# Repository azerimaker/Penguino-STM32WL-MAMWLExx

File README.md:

# Penguino-STM32WL-MAMWLExx
This repo contains all the necessary design and fabrication files for the [Move Solution's MAMWLExx](https://www.hackster.io/move-solutions/design-a-lora-communication-board-based-on-mamwlexx-cbf25c) based Penguino STM32WL breakout board.

MAMWLExx is a very tiny low power radio module, which can be easily integrated into any PCB to enable it for wireless communication. It measures only 15x16mm and features 52 pins out of which 38 are multi-purpose GPIOs.

### Specs (SoC): 
- [STM32WLE5JC](https://www.st.com/en/microcontrollers-microprocessors/stm32wle5jc.html) Wireless SoC
- ARM Cortex M4 ultra-low-power MCU
- Integrated SX1262 RF transciever
- Frequency range: 150 MHz to 960 MHz.
- Modulation: LoRa®, (G)FSK, (G)MSK and BPSK
- Transmitter power: programmable up to +22 dBm 

### Specs ([MAMWLExx module](](https://www.hackster.io/move-solutions/mamwlexx-9f79eb))): 

Board requirements:
- 4 layers, 1.6mm thickness
- 6mil trace/clearance
- 0.3mm drill

### Contact:
If you have any question or comments about the board please feel free to open an issue discussion or drop me a message at [@azerimaker](https://twitter.com/azerimaker). For any specific questions about the module please get in touch with [ Ferdinando Frediani ](https://www.linkedin.com/in/ferdinando-frediani-982807ab/) of Move Solutions, the creators of this awesome module. 

### License:
- Hardware license: CERN-OHL-S v2
- Software license: under MIT unless otherise indicated 
- Documentation license:  CC BY-SA 4.0 International.

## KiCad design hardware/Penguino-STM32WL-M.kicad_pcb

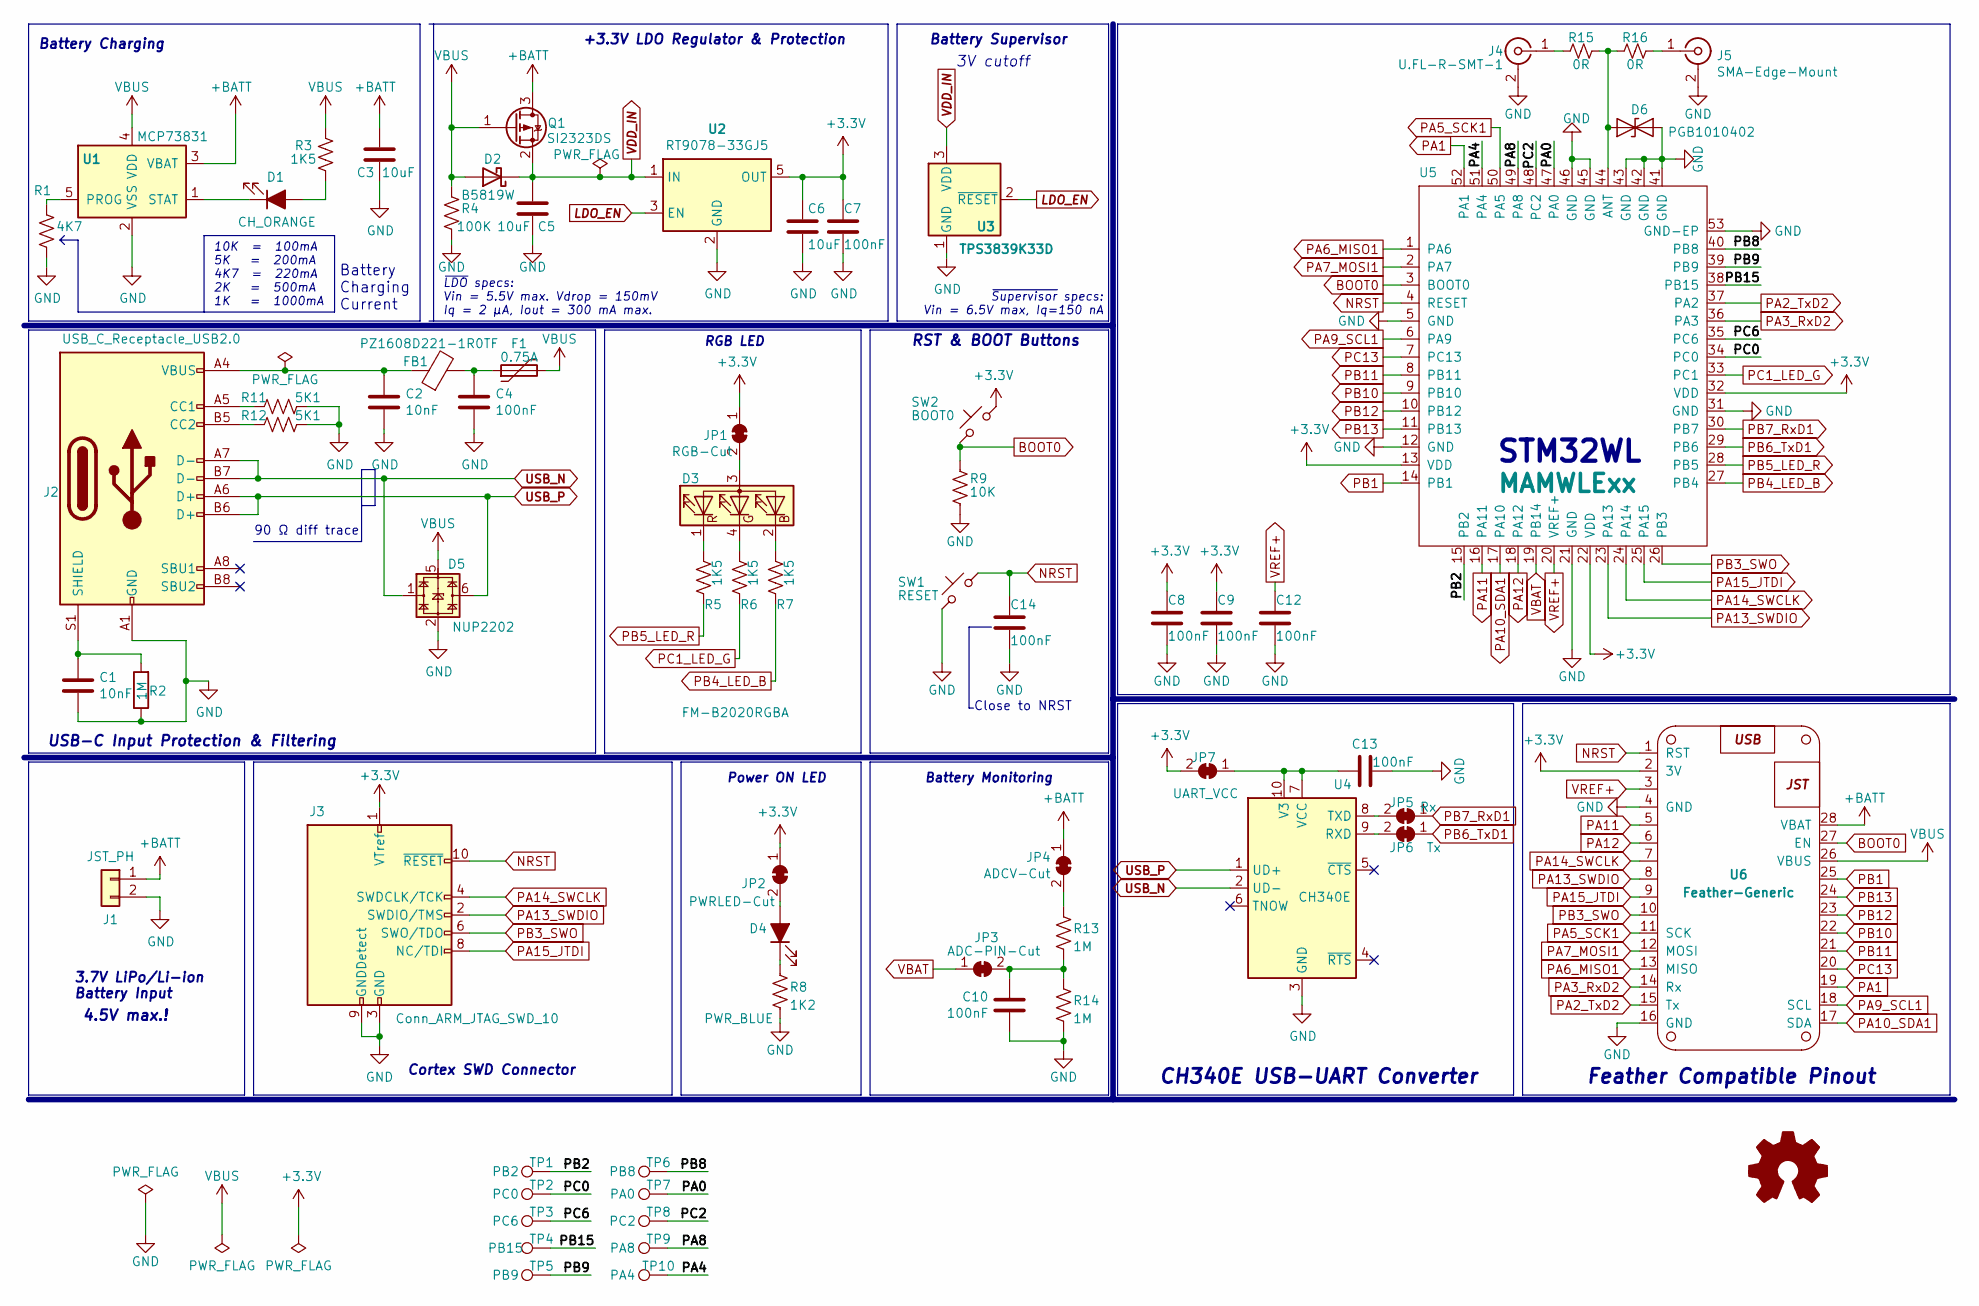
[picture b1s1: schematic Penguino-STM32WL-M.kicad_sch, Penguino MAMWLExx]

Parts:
C1, C2: 10nF; C_0402_1005Metric; MPN CC0402KRX7R9BB103; LCSC_Part# C57112
C3, C5, C6: 10uF; C_0603_1608Metric; MPN CC0603KRX5R6BB106; LCSC_Part# C19702
C4, C7, C8, C9, C12, C14: 100nF; C_0402_1005Metric; MPN GRM155R61A104KA01D; LCSC_Part# C14663
C10, C13: 100nF; C_0402_1005Metric; MPN GRM155R61A104KA01D; LCSC_Part# C1525
D1: CH_ORANGE; LED_0603_1608Metric; MPN 19-217-Y5C-AM1N1VY-3T; LCSC_Part# C375450
D2: B5819W; D_SOD-123; MPN B5819W; LCSC_Part# C8598
D3: FM-B2020RGBA; LED_Cree-PLCC4_2x2mm_CW; MPN FM-B2020RGBA-HG; LCSC_Part# C108793
D4: PWR_BLUE; LED_0603_1608Metric; MPN 19-217/BHC-ZL1M2RY/3T; LCSC_Part# C72041
D5: NUP2202; SOT-363_SC-70-6; MPN NUP2202; LCSC_Part# C502602
D6: PGB1010402; L_0402_1005Metric; MPN PGB1010402KR
F1: 0.75A; Fuse_0805_2012Metric; MPN SMD0805P075TF; LCSC_Part# C20979
FB1: PZ1608D221-1R0TF; L_0603_1608Metric; MPN PZ1608D221-1R0TF; LCSC_Part# C98286
J1: JST_PH; JST_PH_S2B-PH-SM4-TB_1x02-1MP_P2.00mm_Horizontal; MPN S2B-PH-SM4-TB(LF)(SN)
J2: USB_C_Receptacle_USB2.0; USB_C_Receptacle_HRO_TYPE-C-31-M-12; MPN TYPE-C-31-M-12
J3: Conn_ARM_JTAG_SWD_10; PinHeader_2x05_P1.27mm_Vertical_SMD; MPN 20021121-00010C4LF
J4: U.FL-R-SMT-1; U.FL_Hirose_U.FL-R-SMT-1_Vertical; MPN U.FL-R-SMT-1(80)
J5: SMA-Edge-Mount; SMA_J_P_X_ST_EM1_EdgeMount
JP1: RGB-Cut; SolderJumper-2_P1.3mm_Bridged_RoundedPad1.0x1.5mm
JP2: PWRLED-Cut; SolderJumper-2_P1.3mm_Bridged_RoundedPad1.0x1.5mm
JP3: ADC-PIN-Cut; SolderJumper-2_P1.3mm_Bridged_RoundedPad1.0x1.5mm
JP4: ADCV-Cut; SolderJumper-2_P1.3mm_Bridged_RoundedPad1.0x1.5mm
JP5: Rx; SolderJumper-2_P1.3mm_Bridged_RoundedPad1.0x1.5mm
JP6: Tx; SolderJumper-2_P1.3mm_Bridged_RoundedPad1.0x1.5mm
JP7: UART_VCC; SolderJumper-2_P1.3mm_Bridged_RoundedPad1.0x1.5mm
Q1: SI2323DS; SOT-23; MPN SI2323DS; LCSC_Part# C2593
R1: 4K7; R_0402_1005Metric; MPN RC0402JR-074K7L; LCSC_Part# C25900
R2, R13: 1M; R_0402_1005Metric; MPN RC0402JR-071ML; LCSC_Part# C26083
R3: 1K5; R_0402_1005Metric; MPN RC0402JR-071K5L
R4: 100K; R_0402_1005Metric; MPN RC0402JR-07100KL; LCSC_Part# C25741
R5, R6, R7: 1K5; R_0402_1005Metric; MPN RC0402JR-071K5L; LCSC_Part# C25862
R8: 1K2; R_0402_1005Metric; MPN 0402WGF1201TCE; LCSC_Part# C25862
R9: 10K; R_0402_1005Metric; MPN 0402WGF1201TCE; LCSC_Part# C25862
R11, R12: 5K1; R_0402_1005Metric; MPN RC0402FR-075K1L
R14: 1M; R_0402_1005Metric; MPN RC0402JR-071ML
R15, R16: 0R; R_0402_1005Metric; MPN RC0402JR-070RL
SW1: RESET; SW_Push_SKRPACE010; MPN SKRPACE010
SW2: BOOT0; SW_Push_SKRPACE010; MPN SKRPACE010
TP1: PB2; TestPoint_Pad_D1.0mm
TP2: PC0; TestPoint_Pad_D1.0mm
TP3: PC6; TestPoint_Pad_D1.0mm
TP4: PB15; TestPoint_Pad_D1.0mm
TP5: PB9; TestPoint_Pad_D1.0mm
TP6: PB8; TestPoint_Pad_D1.0mm
TP7: PA0; TestPoint_Pad_D1.0mm
TP8: PC2; TestPoint_Pad_D1.0mm
TP9: PA8; TestPoint_Pad_D1.0mm
TP10: PA4; TestPoint_Pad_D1.0mm
U1: MCP73831; SOT-23-5; MPN MCP73831T-2ACI/OT; LCSC_Part# C424093
U2: RT9078-33GJ5; TSOT-23-5; MPN RT9078-33GJ5; LCSC_Part# C110427
U3: TPS3839K33D; SOT-23; MPN TPS3839K33D; LCSC_Part# C9965
U4: CH340E; MSOP-10_3x3mm_P0.5mm; MPN CH340E; LCSC_Part# C99652
U5: MAMWLExx; stm32wl-mamwlexx-module-footprint_w_s_paste; MPN MAMWLExx
U6: Feather-Generic

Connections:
+3V3: C6.1, C7.1, C8.1, C9.1, J3.1 (VTref), JP1.1 (A), JP2.1 (A), JP7.2 (B), SW2.2, U2.5 (OUT), U5.13 (VDD), U5.22 (VDD), U5.32 (VDD), U6.2 (3V)
+BATT: C3.1, J1.1, JP4.1 (A), Q1.3 (D), U1.3 (VBAT), U6.28 (VBAT)
/PA0: TP7.1, U5.47 (PA0)
/PA4: TP10.1, U5.51 (PA4)
/PA8: TP9.1, U5.49 (PA8)
/PB2: TP1.1, U5.15 (PB2)
/PB8: TP6.1, U5.40 (PB8)
/PB9: TP5.1, U5.39 (PB9)
/PB15: TP4.1, U5.38 (PB15)
/PC0: TP2.1, U5.34 (PC0)
/PC2: TP8.1, U5.48 (PC2)
/PC6: TP3.1, U5.35 (PC6)
BOOT0: R9.1, SW2.1, U5.3 (BOOT0), U6.27 (EN)
GND: C1.1, C2.2, C3.2, C4.2, C5.2, C6.2, C7.2, C8.2, C9.2, C10.1, C12.2, C13.2, C14.2, D5.2, D6.1 (A1), J1.2, J2.A1 (GND), J2.A12 (GND), J2.B1 (GND), J2.B12 (GND), J3.3 (GND), J3.5 (GND), J3.9 (GNDDetect), J4.2 (Ext), J5.2 (Ext), R1.2, R2.1, R4.2, R8.2, R9.2, R11.1, R12.1, R14.2, SW1.1, U1.2 (VSS), U2.2 (GND), U3.1 (GND), U4.3 (GND), U5.5 (GND), U5.12 (GND), U5.21 (GND), U5.31 (GND), U5.41 (GND), U5.42 (GND), U5.43 (GND), U5.45 (GND), U5.46 (GND), U5.53 (GND-EP), U5.54 (GND-EP), U5.55 (GND-EP), U5.56 (GND-EP), U5.57 (GND-EP), U5.58 (GND-EP), U5.59 (GND-EP), U5.60 (GND-EP), U5.61 (GND-EP), U5.62 (GND-EP), U5.63 (GND-EP), U5.64 (GND-EP), U5.65 (GND-EP), U5.66 (GND-EP), U6.4 (GND), U6.16 (GND)
LDO_EN: U2.3 (EN), U3.2 (~RESET)
NRST: C14.1, J3.10 (~RESET), SW1.2, U5.4 (RESET), U6.1 (RST)
unnamed: C1.2, J2.S1 (SHIELD), R2.2
unnamed: C2.1, FB1.1, J2.A4 (VBUS), J2.A9 (VBUS), J2.B4 (VBUS), J2.B9 (VBUS)
unnamed: C4.1, F1.1, FB1.2
unnamed: C10.2, JP3.2 (B), R13.2, R14.1
unnamed: C13.1, JP7.1 (A), U4.7 (VCC), U4.10 (V3)
unnamed: D1.1 (K), U1.1 (STAT)
unnamed: D1.2 (A), R3.2
unnamed: D3.1 (RK), R5.1
unnamed: D3.2 (BK), R7.1
unnamed: D3.3 (A), JP1.2 (B)
unnamed: D3.4 (GK), R6.1
unnamed: D4.1 (K), R8.1
unnamed: D4.2 (A), JP2.2 (B)
unnamed: D6.2 (A2), R15.1, R16.2, U5.44 (ANT)
unnamed: J2.A5 (CC1), R11.2
unnamed: J2.B5 (CC2), R12.2
unnamed: J4.1 (In), R15.2
unnamed: J5.1 (In), R16.1
unnamed: JP4.2 (B), R13.1
unnamed: JP5.2 (B), U4.8 (TXD)
unnamed: JP6.2 (B), U4.9 (RXD)
unnamed: R1.1, U1.5 (PROG)
PA1: U5.52 (PA1), U6.19
PA2_TxD2: U5.37 (PA2), U6.15 (Tx)
PA3_RxD2: U5.36 (PA3), U6.14 (Rx)
PA5_SCK1: U5.50 (PA5), U6.11 (SCK)
PA6_MISO1: U5.1 (PA6), U6.13 (MISO)
PA7_MOSI1: U5.2 (PA7), U6.12 (MOSI)
PA9_SCL1: U5.6 (PA9), U6.18 (SCL)
PA10_SDA1: U5.17 (PA10), U6.17 (SDA)
PA11: U5.16 (PA11), U6.5
PA12: U5.18 (PA12), U6.6
PA13_SWDIO: J3.2 (SWDIO/TMS), U5.23 (PA13), U6.8
PA14_SWCLK: J3.4 (SWDCLK/TCK), U5.24 (PA14), U6.7
PA15_JTDI: J3.8 (NC/TDI), U5.25 (PA15), U6.9
PB1: U5.14 (PB1), U6.25
PB3_SWO: J3.6 (SWO/TDO), U5.26 (PB3), U6.10
PB4_LED_B: R7.2, U5.27 (PB4)
PB5_LED_R: R5.2, U5.28 (PB5)
PB6_TxD1: JP6.1 (A), U5.29 (PB6)
PB7_RxD1: JP5.1 (A), U5.30 (PB7)
PB10: U5.9 (PB10), U6.22
PB11: U5.8 (PB11), U6.21
PB12: U5.10 (PB12), U6.23
PB13: U5.11 (PB13), U6.24
PC1_LED_G: R6.2, U5.33 (PC1)
PC13: U5.7 (PC13), U6.20
USB_N: D5.1, J2.A7 (D-), J2.B7 (D-), U4.2 (UD-)
USB_P: D5.6, J2.A6 (D+), J2.B6 (D+), U4.1 (UD+)
VBAT: JP3.1 (A), U5.19 (PB14)
VBUS: D2.2 (A), D5.5, F1.2, Q1.1 (G), R3.1, R4.1, U1.4 (VDD), U6.26 (VBUS)
VDD_IN: C5.1, D2.1 (K), Q1.2 (S), U2.1 (IN), U3.3 (VDD)
VREF+: C12.1, U5.20 (VREF+), U6.3

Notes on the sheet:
Battery Charging Current
Power ON LED
Cortex SWD Connector
Battery Monitoring
~{LDO} specs: Vin = 5.5V max. Vdrop = 150mV Iq = 2 μA, Iout = 300 mA max.
90 Ω diff trace
Battery Supervisor
10K = 100mA 5K = 200mA 4K7 = 220mA 2K = 500mA 1K = 1000mA
3V cutoff
USB-C Input Protection & Filtering
4.5V max.!
RGB LED
CH340E USB-UART Converter
STM32WL
Feather Compatible Pinout
3.7V LiPo/Li-ion Battery Input
RST & BOOT Buttons
+3.3V LDO Regulator & Protection
Battery Charging
~{Supervisor} specs: Vin = 6.5V max, Iq=150 nA
Close to NRST

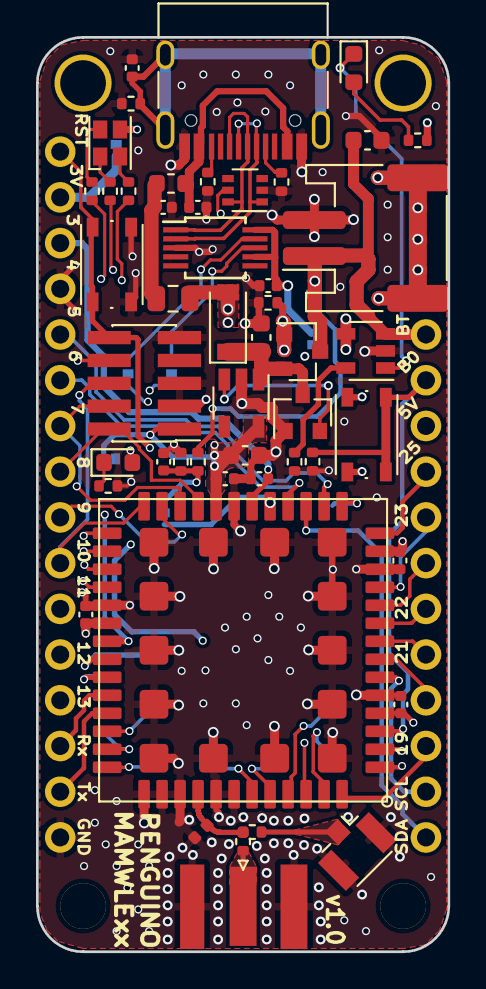
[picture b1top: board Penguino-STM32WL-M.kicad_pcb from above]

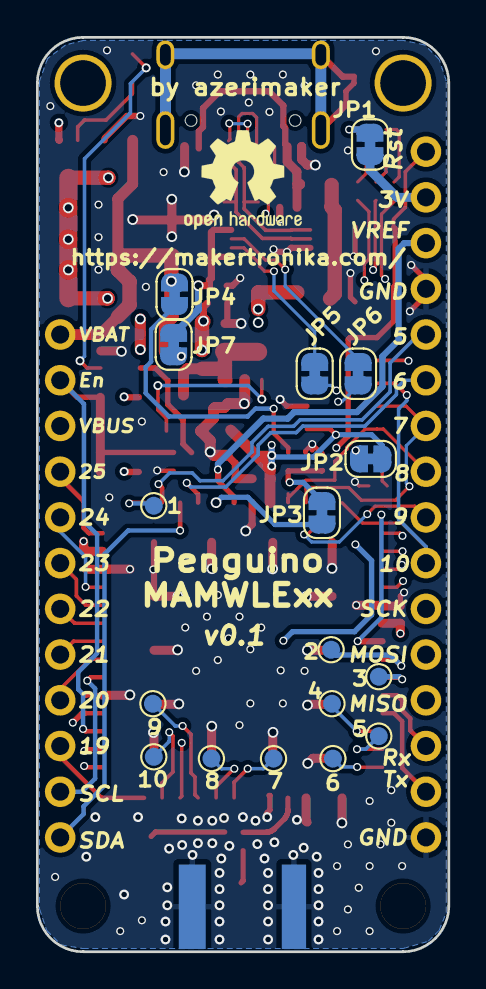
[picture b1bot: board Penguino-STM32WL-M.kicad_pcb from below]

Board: 4 copper layers, 22.9 x 50.8 mm, 67 parts (17 on the bottom side), 69 nets.

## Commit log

2021-04-09 sch, pcb, doc: Add initial version of the design
2021-04-09 fix: Readme update
2021-04-09 fix: Readme
2021-04-09 lib: Add iBOM file
2021-09-16 add: STM32CubeIDE Project Examples
    RGB Toggle and LoRaWAN example.
    LoRaWAN end node example uses USART2 on PA2 and PA3 (Feather pins 14 and 15)
    add: BOM list
2023-12-17 fw: Examples fixed
2023-12-26 hw, fw: Examples added, KiCAD version upgraded
